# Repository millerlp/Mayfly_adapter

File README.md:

# Mayfly_adapter
A circuit board for interfacing 8 analog sensors with an EnviroDIY Mayfly v1.1 data logger. 
This can be used to monitor multiple simple analog voltage inputs. Using the software library
linked below, the user can cycle through 8 inputs of an analog multiplexer (TMUX1208PWR, Texas Instruments) and send the chosen
voltage signal to the analog-to-digital convertor of the Mayfly data logger. The board also has
an 8-channel port expander (PCA9557PWR) that can be used to toggle the SLEEP pin of an attached analog
sensor like the Allegro A1395 Hall effect sensor that this board is designed for. 

As of 2025, the RevB hardware files are functional and in use. These can be used to 
produce a printed circuit board that can be populated with the parts listed in the
file Mayfly_adapter_v1p1_revB_parts.xlsx. 

While the circuit board contains circuits for reading 8 multiplexed analog inputs and
8 multiplexed I2C lines, only the analog input lines are implemented in the associated
library found at [https://github.com/millerlp/Allegro_A139x_8channel_mux](https://github.com/millerlp/Allegro_A139x_8channel_mux). 

Note that this 8-Channel library also relies on a modified library for the PCA9557 library 
found here: [https://github.com/millerlp/pca9557](https://github.com/millerlp/pca9557)

On the bottom of the Mayfly data logger board, some of the solder jumpers should be 
modified: 

On solder jumper 19 (SJ19), move the solder blob from 12 to 13. 
On solder jumper 16 (SJ16), place a blob of solder (activates modem power LED - white)
On solder jumper 17 (SJ17), place a blob of solder (activates modem network indicator LED - blue)

Developed by Luke Miller

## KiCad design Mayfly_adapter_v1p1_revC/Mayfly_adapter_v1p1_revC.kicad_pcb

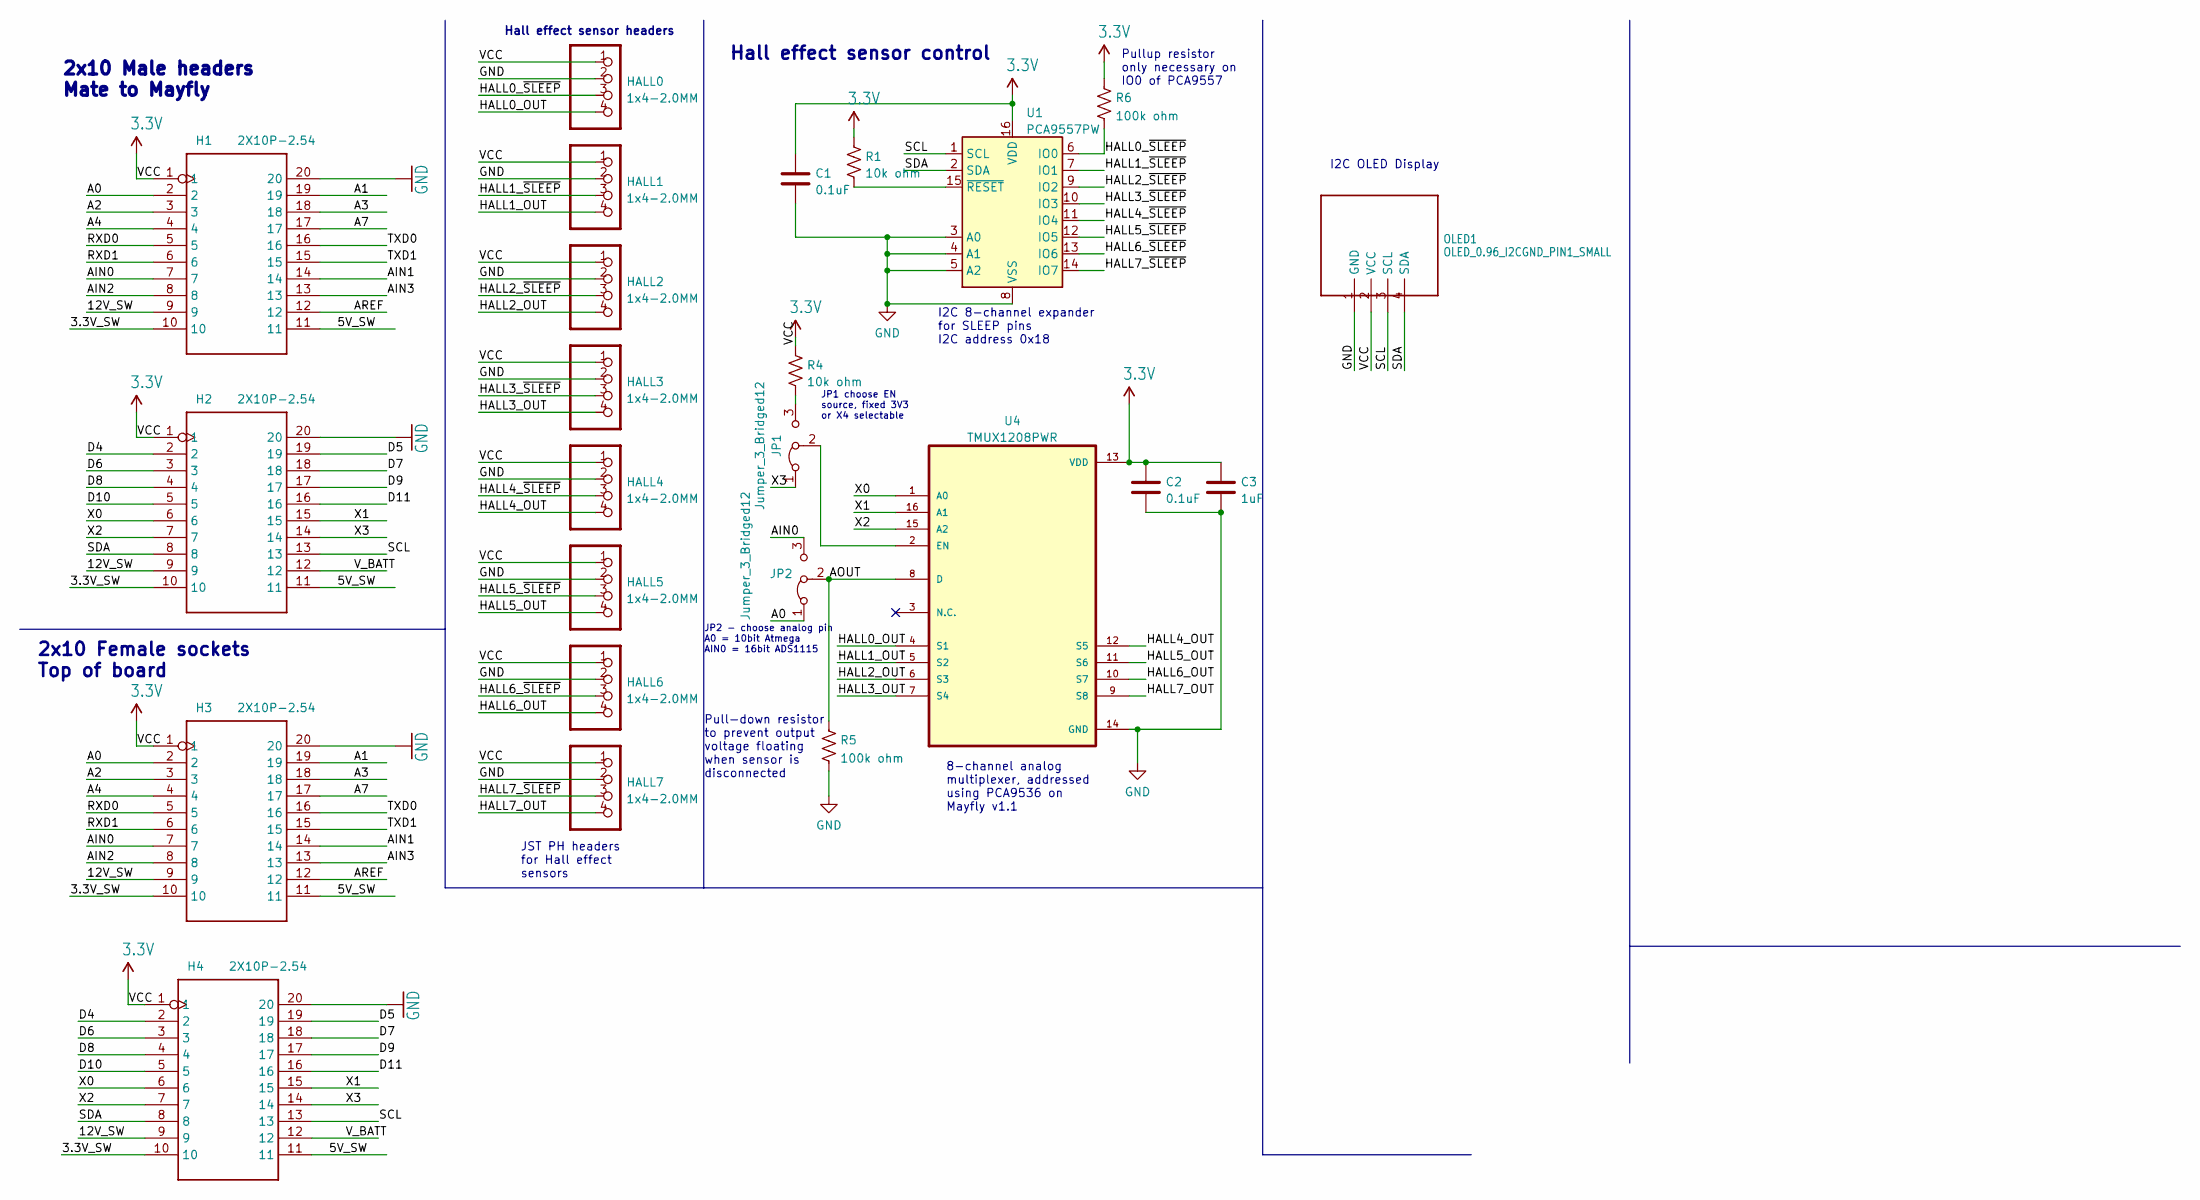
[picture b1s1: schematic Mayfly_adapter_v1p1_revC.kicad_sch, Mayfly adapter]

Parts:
C1, C2: 0.1uF; C_0603_1608Metric
C3: 1uF; C_0603_1608Metric
H1, H2, H3, H4: 2X10P-2.54; H2X10-2.54
HALL0, HALL1, HALL2, HALL3, HALL4, HALL5, HALL6, HALL7: 1x4-2.0MM; JST_PH_B4B-PH-K_04x2.00mm_Straight
JP1, JP2: Jumper_3_Bridged12; SolderJumper-3_P1.3mm_Bridged12_RoundedPad1.0x1.5mm
OLED1: OLED_0.96_I2CGND_PIN1_SMALL; Display_128x64_096_I2C
R1, R4: 10k ohm; R_0603_1608Metric
R5, R6: 100k ohm; R_0603_1608Metric
U1: PCA9557PW; TSSOP-16_4.4x5mm_P0.65mm
U4: TMUX1208PWR; SOP65P640X120-16N

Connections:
3.3V: C1.1, C2.1, C3.1, H1.1, H2.1, H3.1, H4.1, HALL0.1, HALL1.1, HALL2.1, HALL3.1, HALL4.1, HALL5.1, HALL6.1, HALL7.1, OLED1.2 (VCC), R1.1, R4.1, R6.1, U1.16 (VDD), U4.13 (VDD)
/3.3V_SW: H1.10, H2.10, H3.10, H4.10
/5V_SW: H1.11, H2.11, H3.11, H4.11
/12V_SW: H1.9, H2.9, H3.9, H4.9
/A0: H1.2, H3.2, JP2.1 (A)
/A1: H1.19, H3.19
/A2: H1.3, H3.3
/A3: H1.18, H3.18
/A4: H1.4, H3.4
/A7: H1.17, H3.17
/AIN0: H1.7, H3.7, JP2.3 (B)
/AIN1: H1.14, H3.14
/AIN2: H1.8, H3.8
/AIN3: H1.13, H3.13
/AOUT: JP2.2 (C), R5.1, U4.8 (D)
/AREF: H1.12, H3.12
/D4: H2.2, H4.2
/D5: H2.19, H4.19
/D6: H2.3, H4.3
/D7: H2.18, H4.18
/D8: H2.4, H4.4
/D9: H2.17, H4.17
/D10: H2.5, H4.5
/D11: H2.16, H4.16
/HALL0_OUT: HALL0.4, U4.4 (S1)
/HALL0_~SLEEP: HALL0.3, R6.2, U1.6 (IO0)
/HALL1_OUT: HALL1.4, U4.5 (S2)
/HALL1_~SLEEP: HALL1.3, U1.7 (IO1)
/HALL2_OUT: HALL2.4, U4.6 (S3)
/HALL2_~SLEEP: HALL2.3, U1.9 (IO2)
/HALL3_OUT: HALL3.4, U4.7 (S4)
/HALL3_~SLEEP: HALL3.3, U1.10 (IO3)
/HALL4_OUT: HALL4.4, U4.12 (S5)
/HALL4_~SLEEP: HALL4.3, U1.11 (IO4)
/HALL5_OUT: HALL5.4, U4.11 (S6)
/HALL5_~SLEEP: HALL5.3, U1.12 (IO5)
/HALL6_OUT: HALL6.4, U4.10 (S7)
/HALL6_~SLEEP: HALL6.3, U1.13 (IO6)
/HALL7_OUT: HALL7.4, U4.9 (S8)
/HALL7_~SLEEP: HALL7.3, U1.14 (IO7)
/RXD0: H1.5, H3.5
/RXD1: H1.6, H3.6
/SCL: H2.13, H4.13, OLED1.3 (SCL), U1.1 (SCL)
/SDA: H2.8, H4.8, OLED1.4 (SDA), U1.2 (SDA)
/TXD0: H1.16, H3.16
/TXD1: H1.15, H3.15
/V_BATT: H2.12, H4.12
/X0: H2.6, H4.6, U4.1 (A0)
/X1: H2.15, H4.15, U4.16 (A1)
/X2: H2.7, H4.7, U4.15 (A2)
/X3: H2.14, H4.14, JP1.1 (A)
GND: C1.2, C2.2, C3.2, H1.20, H2.20, H3.20, H4.20, HALL0.2, HALL1.2, HALL2.2, HALL3.2, HALL4.2, HALL5.2, HALL6.2, HALL7.2, OLED1.1 (GND), R5.2, U1.3 (A0), U1.4 (A1), U1.5 (A2), U1.8 (VSS), U4.14 (GND)
unnamed: JP1.3 (B), R4.2
unnamed: JP1.2 (C), U4.2 (EN)
unnamed: R1.2, U1.15 (~RESET)

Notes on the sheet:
Hall effect sensor headers
JST PH headers for Hall effect sensors
Pullup resistor only necessary on IO0 of PCA9557
JP1 choose EN source, fixed 3V3 or X4 selectable
2x10 Female sockets Top of board
JP2 - choose analog pin A0 = 10bit Atmega AIN0 = 16bit ADS1115
I2C OLED Display
I2C 8-channel expander for SLEEP pins I2C address 0x18
Hall effect sensor control
8-channel analog multiplexer, addressed using PCA9536 on Mayfly v1.1
Pull-down resistor to prevent output voltage floating when sensor is disconnected
2x10 Male headers Mate to Mayfly

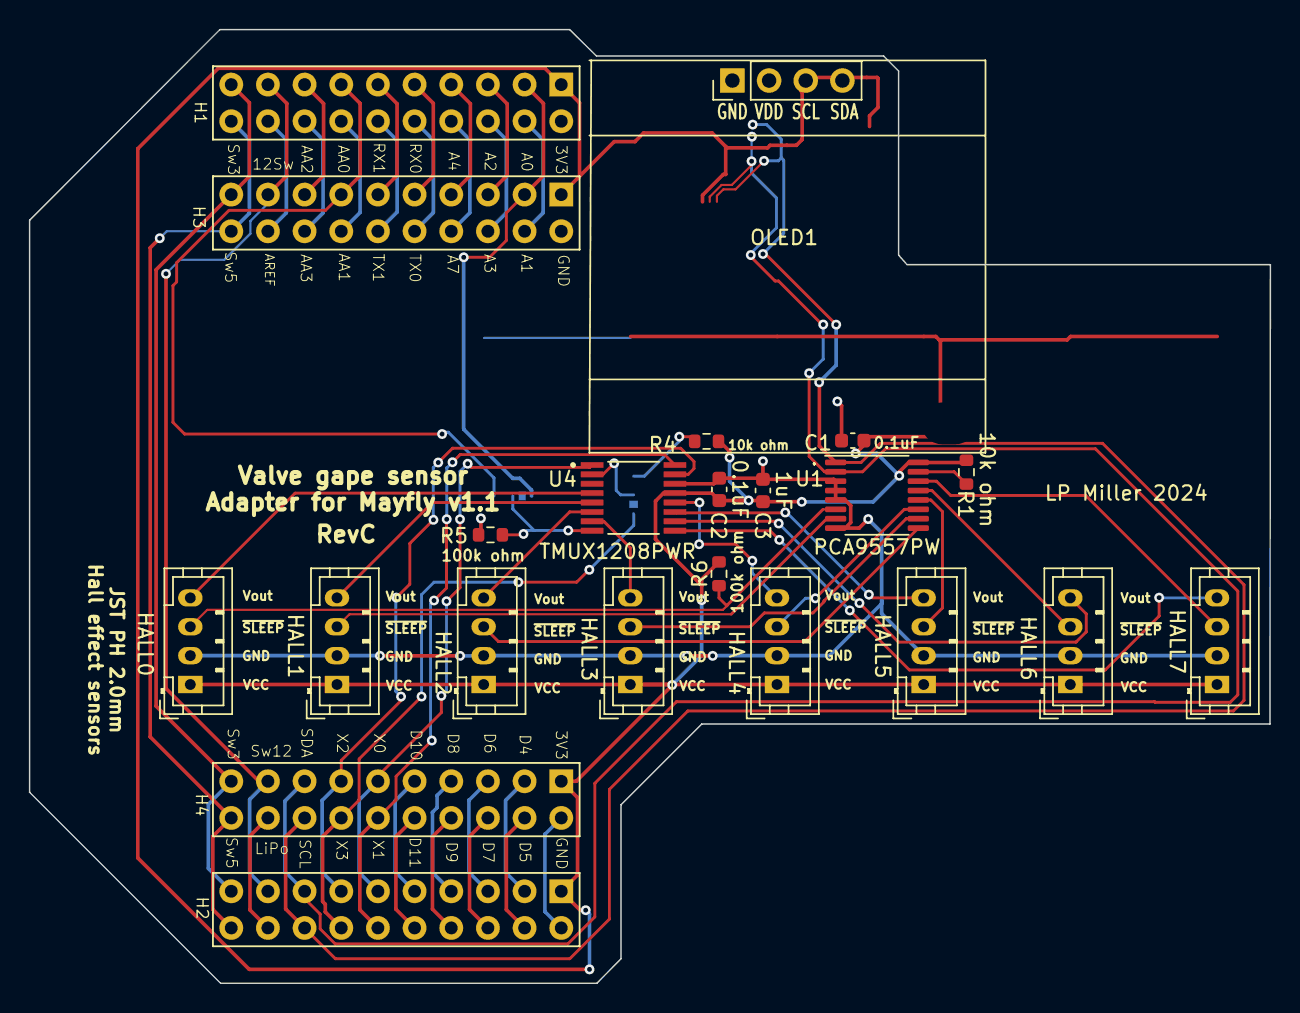
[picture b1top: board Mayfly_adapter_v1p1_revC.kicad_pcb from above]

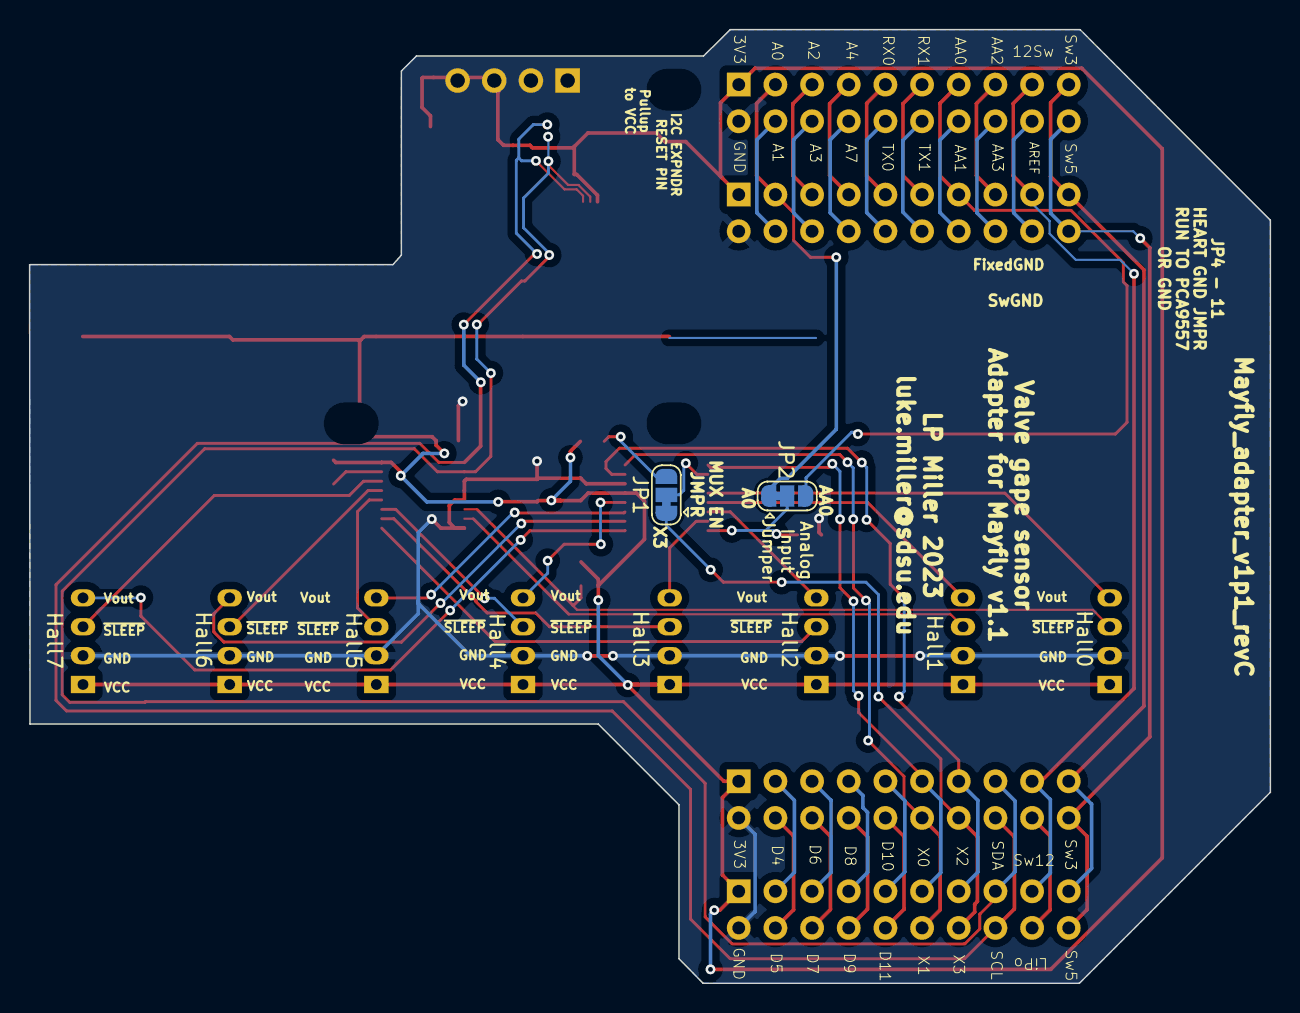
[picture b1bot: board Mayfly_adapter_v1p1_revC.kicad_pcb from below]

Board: 2 copper layers, 86.0 x 66.1 mm, 24 parts (2 on the bottom side), 55 nets.

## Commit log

2025-05-29 Update ignore
2025-05-29 Prototype images
2025-05-29 Rev A
2025-05-29 Rev B - working prototype
    This version was in use 2023-2024
2025-05-29 Rev C is not complete - do not use yet
    Revision C is still a work in progress and is not functional.
2025-05-29 Useful data sheets
2025-05-29 Update the README
2025-05-29 Shrink those pictures a bit
2025-05-29 Lower case file extension
